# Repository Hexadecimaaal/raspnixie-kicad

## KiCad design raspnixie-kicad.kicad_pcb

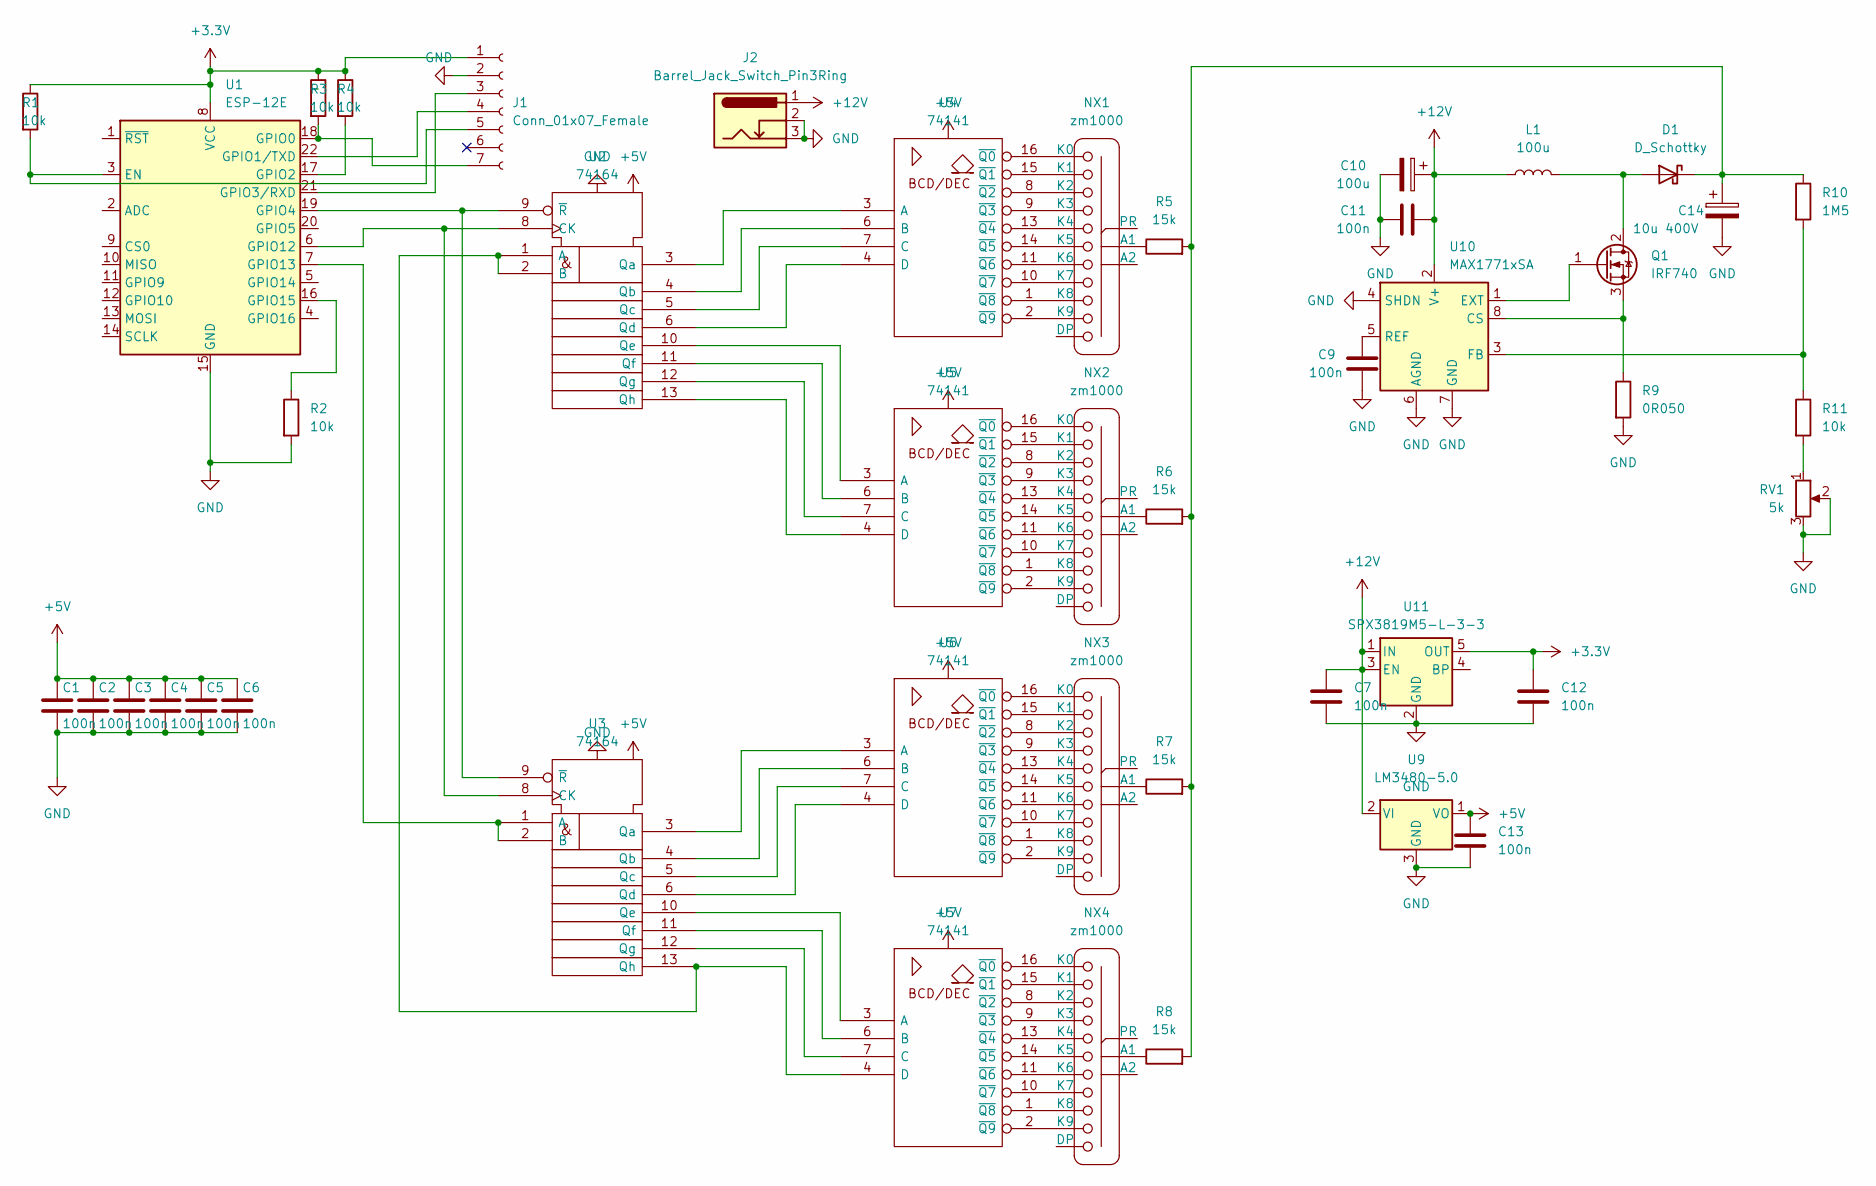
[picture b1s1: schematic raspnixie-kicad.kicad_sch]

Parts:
C1, C2, C3, C4, C5, C6, C7, C9, C11, C12, C13: 100n; C_1206_3216Metric_Pad1.33x1.80mm_HandSolder
C10: 100u; CP_EIA-7343-31_Kemet-D_Pad2.25x2.55mm_HandSolder
C14: 10u 400V; CP_Radial_D10.0mm_P5.00mm
D1: D_Schottky; D_SMB_Handsoldering
J1: Conn_01x07_Female; SOIC-7
J2: Barrel_Jack_Switch_Pin3Ring; BarrelJack_Horizontal
L1: 100u; L_10.4x10.4_H4.8
NX1, NX2, NX3, NX4: zm1000
Q1: IRF740; TO-220-3_Vertical
R1, R2, R3, R4, R11: 10k; R_1206_3216Metric_Pad1.30x1.75mm_HandSolder
R5, R6, R7, R8: 15k; R_1206_3216Metric_Pad1.30x1.75mm_HandSolder
R9: 0R050; R_2010_5025Metric_Pad1.40x2.65mm_HandSolder
R10: 1M5; R_1206_3216Metric_Pad1.30x1.75mm_HandSolder
RV1: 5k; Potentiometer_Bourns_TC33X_Vertical
U1: ESP-12E
U2, U3: 74164; DIP-14_W7.62mm_LongPads
U4, U5, U6, U7: 74141; DIP-16_W7.62mm_LongPads
U9: LM3480-5.0; SOT-23_Handsoldering
U10: MAX1771xSA; SO-8_3.9x4.9mm_P1.27mm
U11: SPX3819M5-L-3-3; SOT-23-5_HandSoldering

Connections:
+3.3V: C12.1, J1.1, R1.1, R3.1, R4.1, U1.8 (VCC), U11.5 (OUT)
+5V: C1.1, C2.1, C3.1, C4.1, C5.1, C6.1, C13.1, U2.14 (Vdd), U3.14 (Vdd), U4.5 (VCC), U5.5 (VCC), U6.5 (VCC), U7.5 (VCC), U9.1 (VO)
+12V: C7.1, C10.1, C11.1, J2.1, L1.1, U9.2 (VI), U10.2 (V+), U11.1 (IN), U11.3 (EN)
GND: C1.2, C2.2, C3.2, C4.2, C5.2, C6.2, C7.2, C9.2, C10.2, C11.2, C12.2, C13.2, C14.2, J1.2, J2.2, J2.3, R2.2, R9.2, RV1.2, RV1.3, U1.15 (GND), U2.7 (Vss), U3.7 (Vss), U4.12 (GND), U5.12 (GND), U6.12 (GND), U7.12 (GND), U9.3 (GND), U10.4 (SHDN), U10.6 (AGND), U10.7 (GND), U11.2 (GND)
unnamed: D1.2 (A), L1.2, Q1.2 (D)
unnamed: C14.1, D1.1 (K), R5.2, R6.2, R7.2, R8.2, R10.1
unnamed: J1.3, U1.21 (GPIO3/RXD)
unnamed: J1.4, U1.22 (GPIO1/TXD)
unnamed: J1.5, R1.2, U1.3 (EN)
unnamed: J1.7, R3.2, U1.18 (GPIO0)
unnamed: NX1.12 (A1), R5.1
unnamed: NX1.0 (K0), U4.16 (~Q0)
unnamed: NX1.1 (K1), U4.15 (~Q1)
unnamed: NX1.2 (K2), U4.8 (~Q2)
unnamed: NX1.3 (K3), U4.9 (~Q3)
unnamed: NX1.4 (K4), U4.13 (~Q4)
unnamed: NX1.5 (K5), U4.14 (~Q5)
unnamed: NX1.6 (K6), U4.11 (~Q6)
unnamed: NX1.7 (K7), U4.10 (~Q7)
unnamed: NX1.8 (K8), U4.1 (~Q8)
unnamed: NX1.9 (K9), U4.2 (~Q9)
unnamed: NX2.12 (A1), R6.1
unnamed: NX2.0 (K0), U5.16 (~Q0)
unnamed: NX2.1 (K1), U5.15 (~Q1)
unnamed: NX2.2 (K2), U5.8 (~Q2)
unnamed: NX2.3 (K3), U5.9 (~Q3)
unnamed: NX2.4 (K4), U5.13 (~Q4)
unnamed: NX2.5 (K5), U5.14 (~Q5)
unnamed: NX2.6 (K6), U5.11 (~Q6)
unnamed: NX2.7 (K7), U5.10 (~Q7)
unnamed: NX2.8 (K8), U5.1 (~Q8)
unnamed: NX2.9 (K9), U5.2 (~Q9)
unnamed: NX3.12 (A1), R7.1
unnamed: NX3.0 (K0), U6.16 (~Q0)
unnamed: NX3.1 (K1), U6.15 (~Q1)
unnamed: NX3.2 (K2), U6.8 (~Q2)
unnamed: NX3.3 (K3), U6.9 (~Q3)
unnamed: NX3.4 (K4), U6.13 (~Q4)
unnamed: NX3.5 (K5), U6.14 (~Q5)
unnamed: NX3.6 (K6), U6.11 (~Q6)
unnamed: NX3.7 (K7), U6.10 (~Q7)
unnamed: NX3.8 (K8), U6.1 (~Q8)
unnamed: NX3.9 (K9), U6.2 (~Q9)
unnamed: NX4.12 (A1), R8.1
unnamed: NX4.0 (K0), U7.16 (~Q0)
unnamed: NX4.1 (K1), U7.15 (~Q1)
unnamed: NX4.2 (K2), U7.8 (~Q2)
unnamed: NX4.3 (K3), U7.9 (~Q3)
unnamed: NX4.4 (K4), U7.13 (~Q4)
unnamed: NX4.5 (K5), U7.14 (~Q5)
unnamed: NX4.6 (K6), U7.11 (~Q6)
unnamed: NX4.7 (K7), U7.10 (~Q7)
unnamed: NX4.8 (K8), U7.1 (~Q8)
unnamed: NX4.9 (K9), U7.2 (~Q9)
unnamed: Q1.1 (G), U10.1 (EXT)
unnamed: Q1.3 (S), R9.1, U10.8 (CS)
unnamed: R11.2, RV1.1
unnamed: R4.2, U1.17 (GPIO2)
unnamed: U1.19 (GPIO4), U2.9 (~R), U3.9 (~R)
unnamed: U1.6 (GPIO12), U2.8 (CK), U3.8 (CK)
unnamed: U1.7 (GPIO13), U3.1 (A), U3.2 (B)
unnamed: R2.1, U1.16 (GPIO15)
unnamed: U2.1 (A), U2.2 (B), U3.13 (Qh), U7.4 (D)
unnamed: U2.3 (Qa), U4.3 (A)
unnamed: U2.4 (Qb), U4.6 (B)
unnamed: U2.5 (Qc), U4.7 (C)
unnamed: U2.6 (Qd), U4.4 (D)
unnamed: U2.10 (Qe), U5.3 (A)
unnamed: U2.11 (Qf), U5.6 (B)
unnamed: U2.12 (Qg), U5.7 (C)
unnamed: U2.13 (Qh), U5.4 (D)
unnamed: U3.3 (Qa), U6.3 (A)
unnamed: U3.4 (Qb), U6.6 (B)
unnamed: U3.5 (Qc), U6.7 (C)
unnamed: U3.6 (Qd), U6.4 (D)
unnamed: U3.10 (Qe), U7.3 (A)
unnamed: U3.11 (Qf), U7.6 (B)
unnamed: U3.12 (Qg), U7.7 (C)
unnamed: R10.2, R11.1, U10.3 (FB)
unnamed: C9.1, U10.5 (REF)

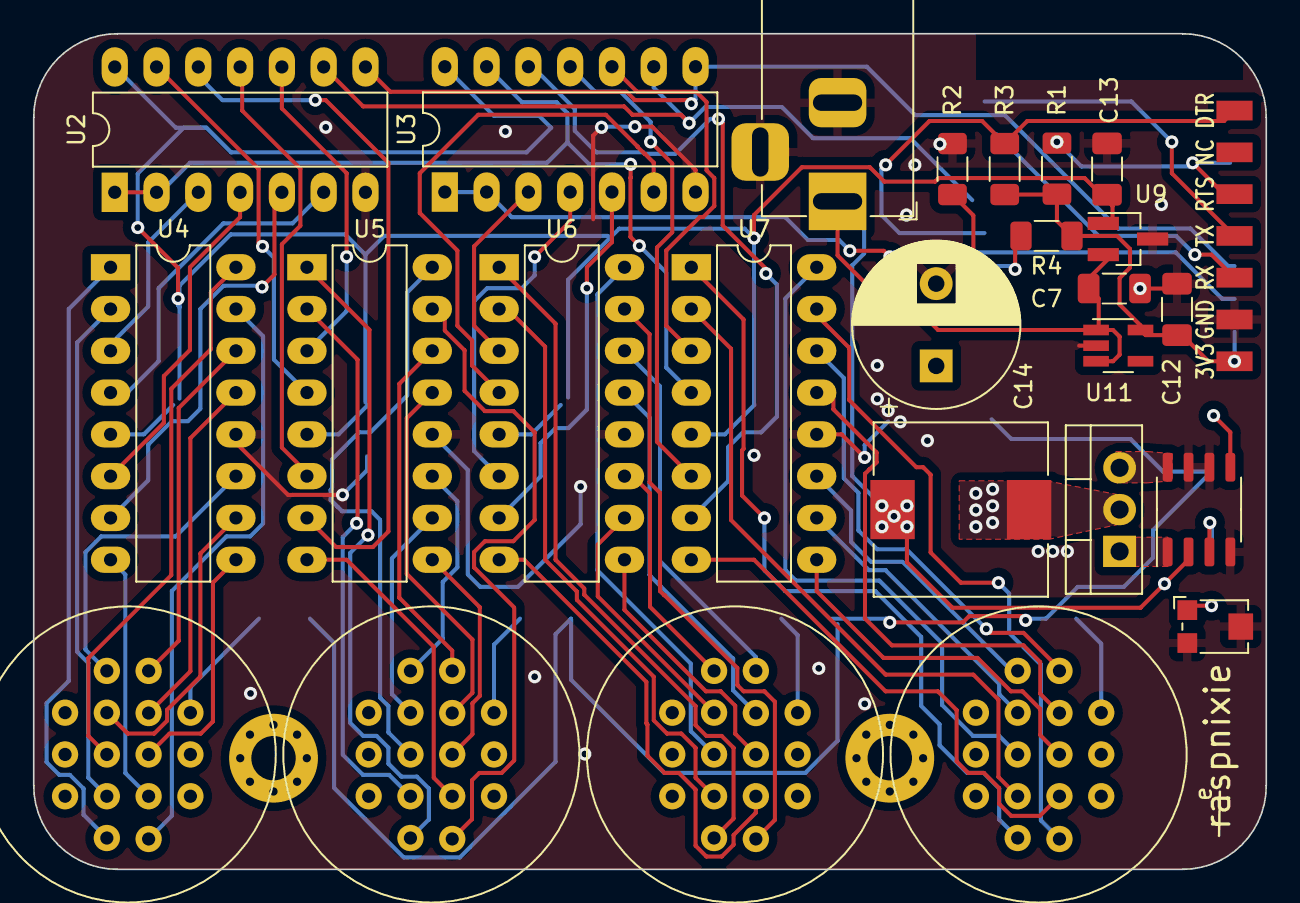
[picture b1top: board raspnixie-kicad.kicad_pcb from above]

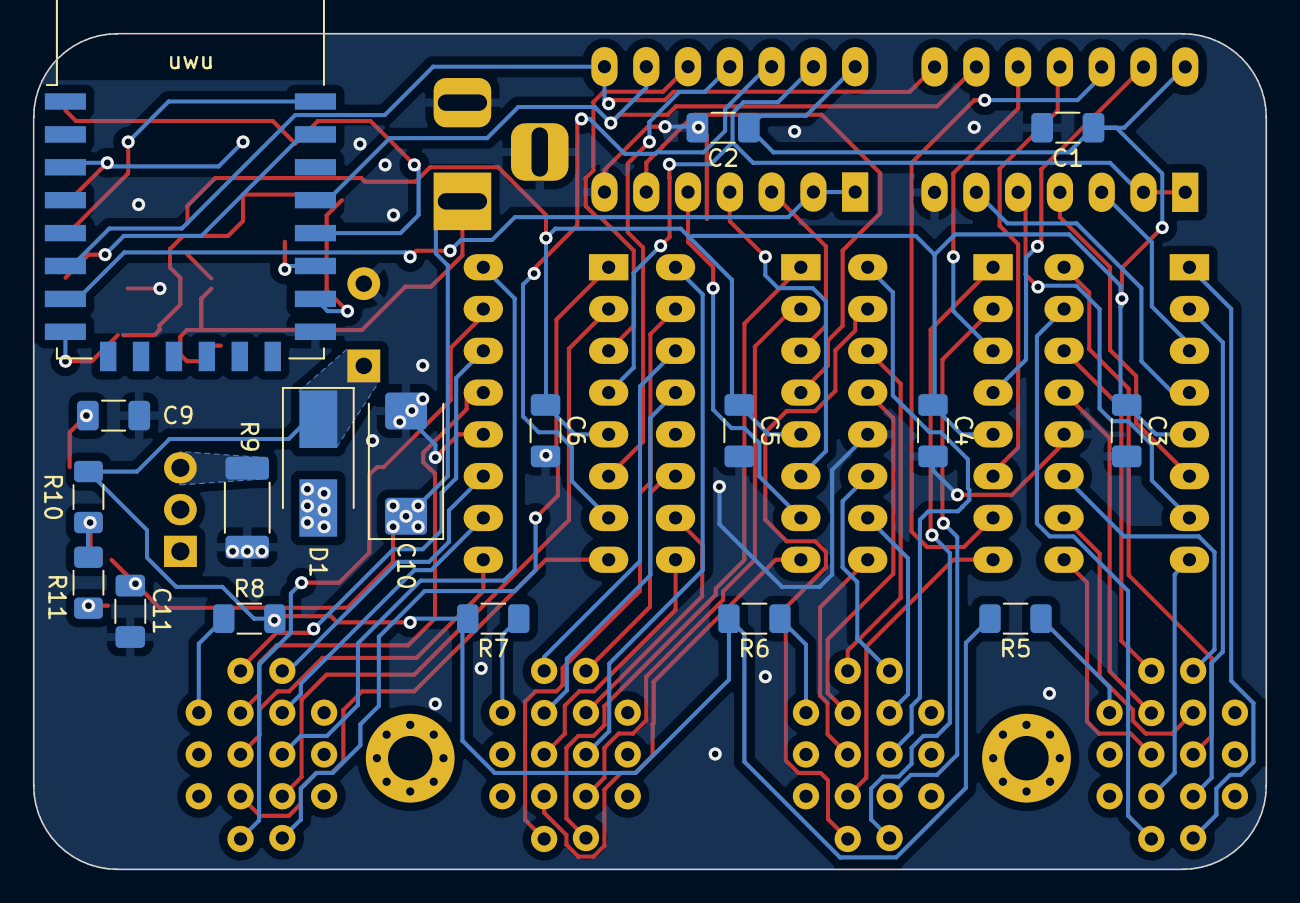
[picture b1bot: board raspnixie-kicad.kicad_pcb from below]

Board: 2 copper layers, 74.9 x 50.8 mm, 44 parts (18 on the bottom side), 80 nets.

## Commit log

2023-07-03 man why is this still ongoing
